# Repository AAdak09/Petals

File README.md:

# Petals
🌸 Petals — A flower key chain with 5 leds.

BOM
Red 5mm LED
6mm Tactile Push Button SW1
CR2032 Battery
5 Resistors
# SCHEMATIC

# PCB

# 3D VIEW

SLACK USERNAME: @Asmita Adak

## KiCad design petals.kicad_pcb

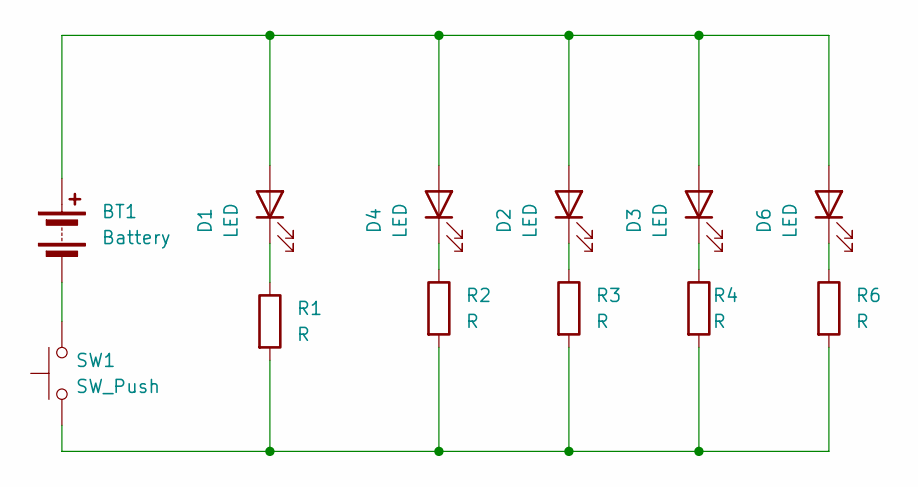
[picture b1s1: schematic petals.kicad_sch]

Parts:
BT1: Battery; BatteryHolder_Keystone_3034_1x20mm
D1, D2, D3, D4, D6: LED; LED_D5.0mm
R1, R2, R3, R4, R6: R; R_Axial_DIN0207_L6.3mm_D2.5mm_P7.62mm_Horizontal
SW1: SW_Push; SW_PUSH_6mm

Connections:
unnamed: BT1.1 (+), D1.2 (A), D2.2 (A), D3.2 (A), D4.2 (A), D6.2 (A)
unnamed: BT1.2 (-), SW1.2
unnamed: D1.1 (K), R1.1
unnamed: D2.1 (K), R3.1
unnamed: D3.1 (K), R4.1
unnamed: D4.1 (K), R2.1
unnamed: D6.1 (K), R6.1
unnamed: R1.2, R2.2, R3.2, R4.2, R6.2, SW1.1

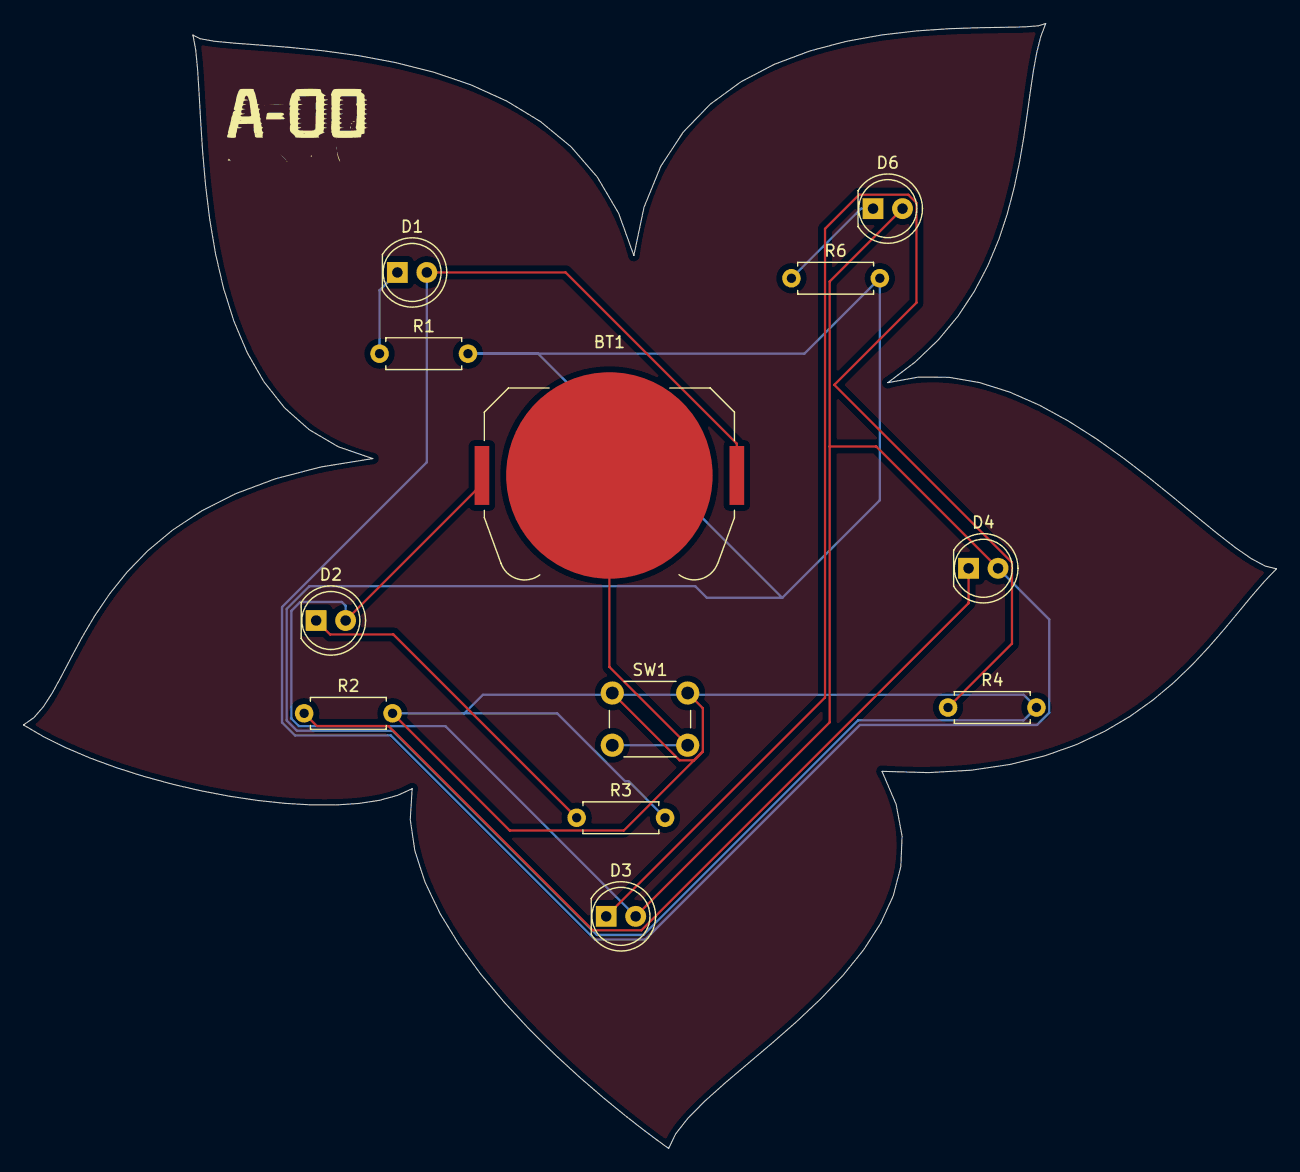
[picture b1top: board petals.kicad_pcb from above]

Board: 2 copper layers, 108.0 x 97.0 mm, 12 parts (0 on the bottom side), 8 nets.
